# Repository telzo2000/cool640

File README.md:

# cool640

<br>

## What is cool640？

cool640 is 4X5 macro pad keyboard.
<br>
If you align the two, you will have a split keyboard.
<br><br>
cool640は4X5のマクロパッドキーボードです。
<br>
cool640は二つ揃えると、分割キーボードになります。
<br><br>
You can choose either pro micro or raspberry pi pico to use.
<br><br>
pro microかraspberry pi picoのどちらか一つを選んで使うことができます。

<br><br>
You can choose either choc switch or cherry mx switch to use.
<br>
Chocスイッチか CHERRY MXスイッチのどちらか一つを選んで使うことができます。

<br>
The size of the PCB is within 100mmX100mm.
<br>
It will be distributed on booth in the future, but you can freely use the data here and place an order with the PCB manufacturer.
<br><br>
PCBのサイズは、100mmX100mm以内です。
<br>
将来、boothにて頒布しますが、ここにあるデータを自由に使い、各自がPCB製造元に発注しても構いません。
<br><br>
I do not take any responsibility for the data that you freely use.
<br>
Please use at your own risk.
<br><br>
各自が自由に使ったデータについては、私は一切の責任を負いません。
<br>
自己責任で利用してください。
<br>

## Build Guide
https://github.com/telzo2000/cool640/blob/main/buildguide_for_cool640.md

<br>

## Firmware
https://github.com/telzo2000/cool640/tree/main/firmware

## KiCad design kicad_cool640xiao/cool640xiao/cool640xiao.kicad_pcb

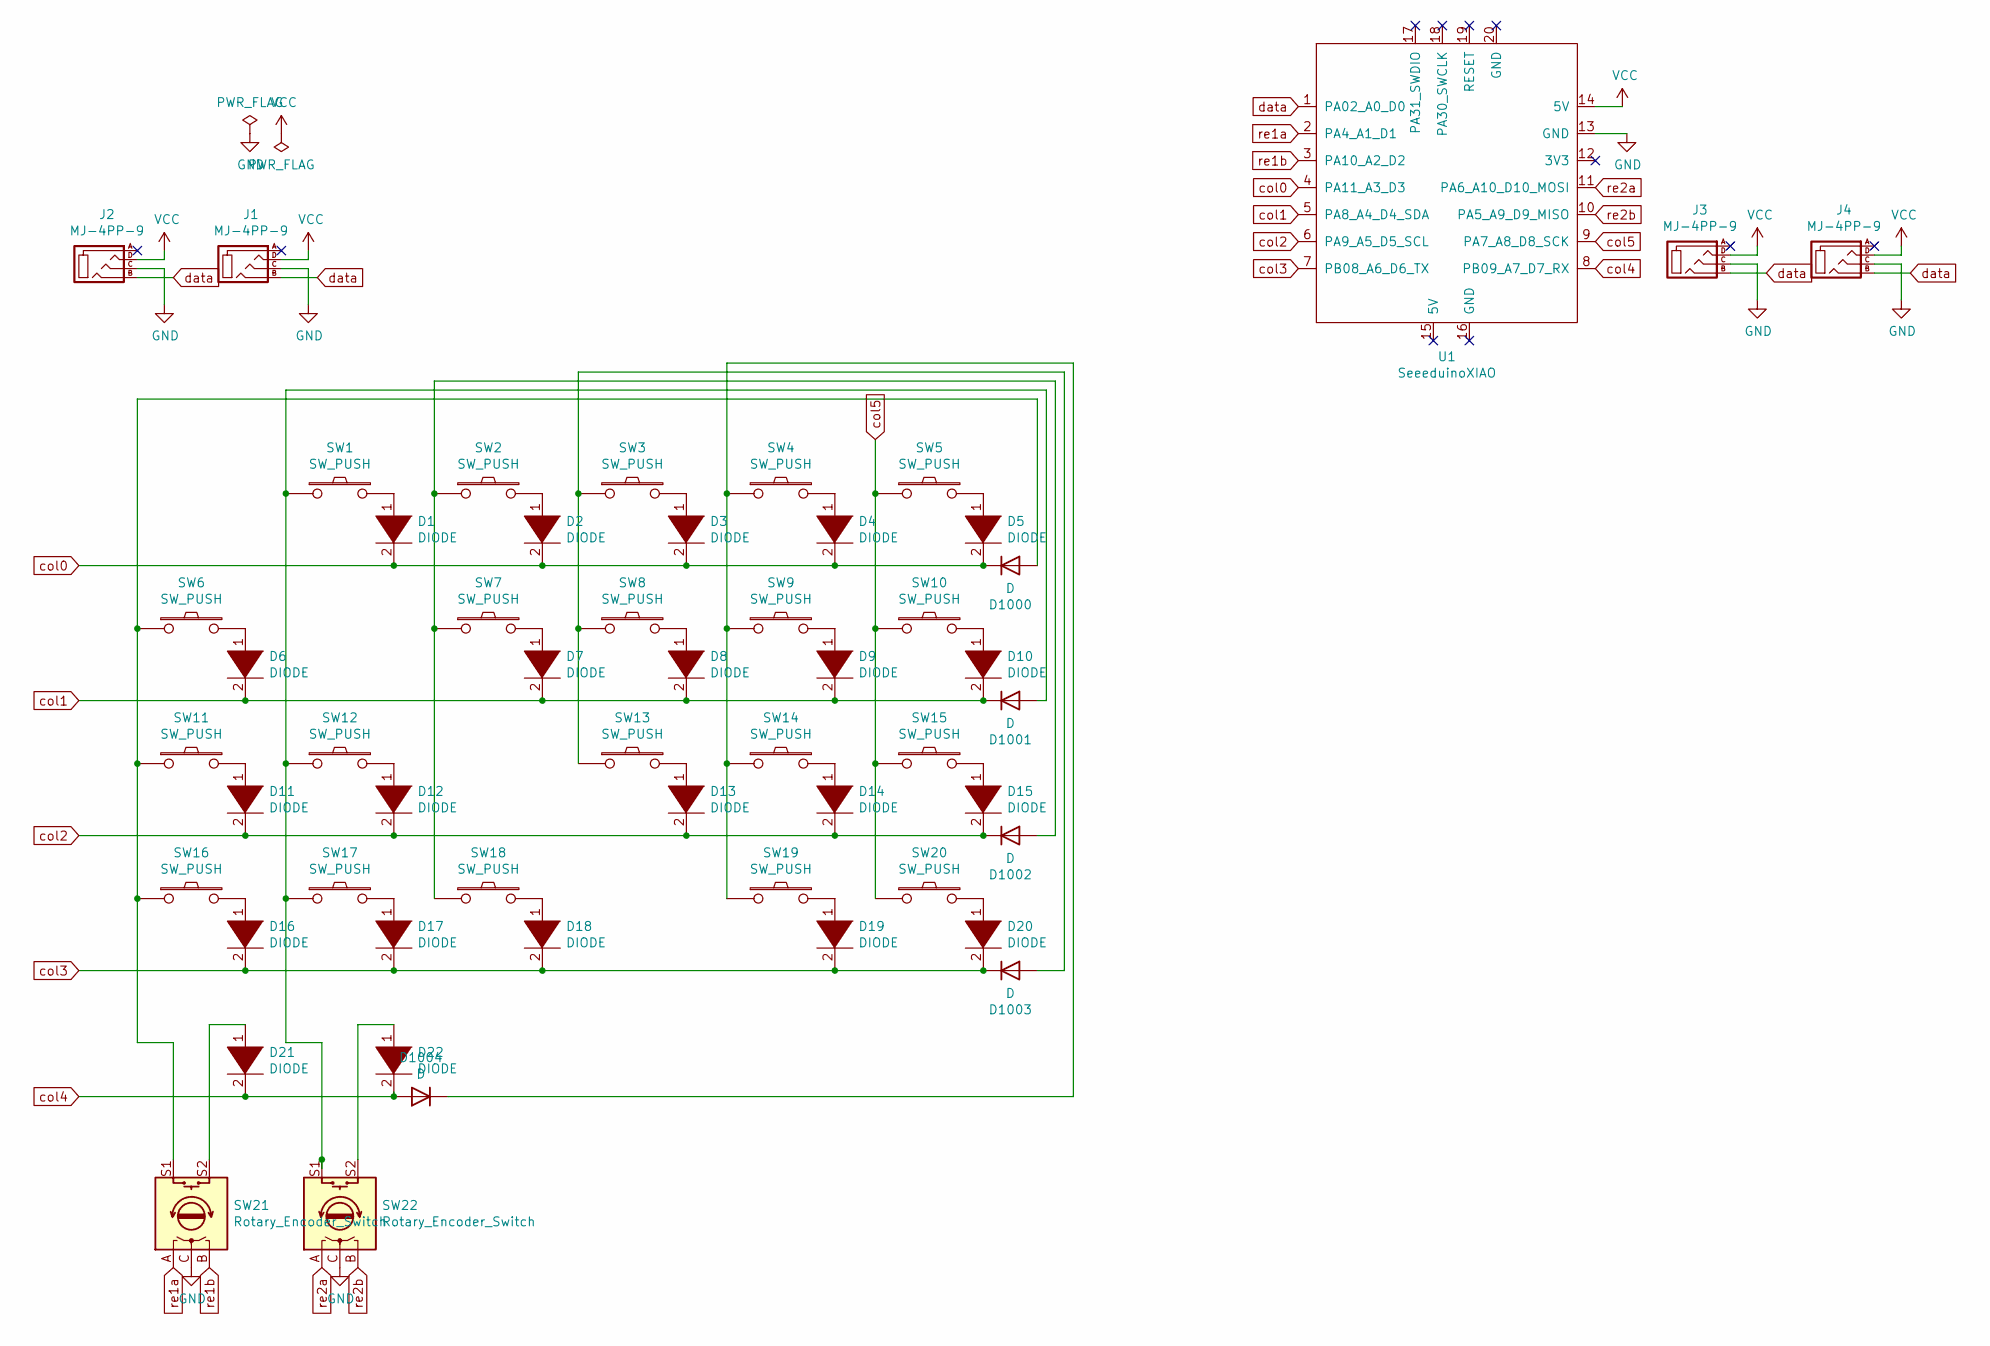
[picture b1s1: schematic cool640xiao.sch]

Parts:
D1, D2, D3, D4, D5, D6, D7, D8, D9, D10, D11, D12, D13, D14, D15, D16, D17, D18, D19, D20, D21, D22: DIODE; D3_TH_SMD
D1000, D1001, D1002, D1003, D1004: D; D3_TH_SMD
J1, J2: MJ-4PP-9; MJ-4PP-9_1side
J3, J4: MJ-4PP-9; TRSpad
SW1, SW2, SW3, SW4, SW5, SW6, SW7, SW8, SW9, SW10, SW11, SW12, SW13, SW14, SW15, SW16, SW17, SW18, SW19, SW20: SW_PUSH; CherryMX_MidHeight_Choc_Hotswap_katagawa
SW21, SW22: Rotary_Encoder_Switch; RotaryEncoder_Alps_EC12E-Switch_Vertical_H20mm_CircularMoun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
U1: SeeeduinoXIAO; XIAO_RP2040

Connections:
GND: J1.C, J2.C, J3.C, J4.C, SW21.C, SW22.C, U1.13 (GND)
unnamed: D1.1 (K), SW1.2
unnamed: D2.1 (K), SW2.2
unnamed: D3.1 (K), SW3.2
unnamed: D4.1 (K), SW4.2
unnamed: D5.1 (K), SW5.2
unnamed: D6.1 (K), SW6.2
unnamed: D7.1 (K), SW7.2
unnamed: D8.1 (K), SW8.2
unnamed: D9.1 (K), SW9.2
unnamed: D10.1 (K), SW10.2
unnamed: D11.1 (K), SW11.2
unnamed: D12.1 (K), SW12.2
unnamed: D13.1 (K), SW13.2
unnamed: D14.1 (K), SW14.2
unnamed: D15.1 (K), SW15.2
unnamed: D16.1 (K), SW16.2
unnamed: D17.1 (K), SW17.2
unnamed: D18.1 (K), SW18.2
unnamed: D19.1 (K), SW19.2
unnamed: D20.1 (K), SW20.2
unnamed: D21.1 (K), SW21.S2
unnamed: D22.1 (K), SW22.S2
unnamed: D1000.2 (A), SW6.1, SW11.1, SW16.1, SW21.S1
unnamed: D1001.2 (A), SW1.1, SW12.1, SW17.1, SW22.S1
unnamed: D1002.2 (A), SW2.1, SW7.1, SW18.1
unnamed: D1003.2 (A), SW3.1, SW8.1, SW13.1
unnamed: D1004.1 (K), SW4.1, SW9.1, SW14.1, SW19.1
VCC: J1.D, J2.D, J3.D, J4.D, U1.14 (5V)
col0: D1.2 (A), D2.2 (A), D3.2 (A), D4.2 (A), D5.2 (A), D1000.1 (K), U1.4 (PA11_A3_D3)
col1: D6.2 (A), D7.2 (A), D8.2 (A), D9.2 (A), D10.2 (A), D1001.1 (K), U1.5 (PA8_A4_D4_SDA)
col2: D11.2 (A), D12.2 (A), D13.2 (A), D14.2 (A), D15.2 (A), D1002.1 (K), U1.6 (PA9_A5_D5_SCL)
col3: D16.2 (A), D17.2 (A), D18.2 (A), D19.2 (A), D20.2 (A), D1003.1 (K), U1.7 (PB08_A6_D6_TX)
col4: D21.2 (A), D22.2 (A), D1004.2 (A), U1.8 (PB09_A7_D7_RX)
col5: SW5.1, SW10.1, SW15.1, SW20.1, U1.9 (PA7_A8_D8_SCK)
data: J1.B, J2.B, J3.B, J4.B, U1.1 (PA02_A0_D0)
re1a: SW21.A, U1.2 (PA4_A1_D1)
re1b: SW21.B, U1.3 (PA10_A2_D2)
re2a: SW22.A, U1.11 (PA6_A10_D10_MOSI)
re2b: SW22.B, U1.10 (PA5_A9_D9_MISO)

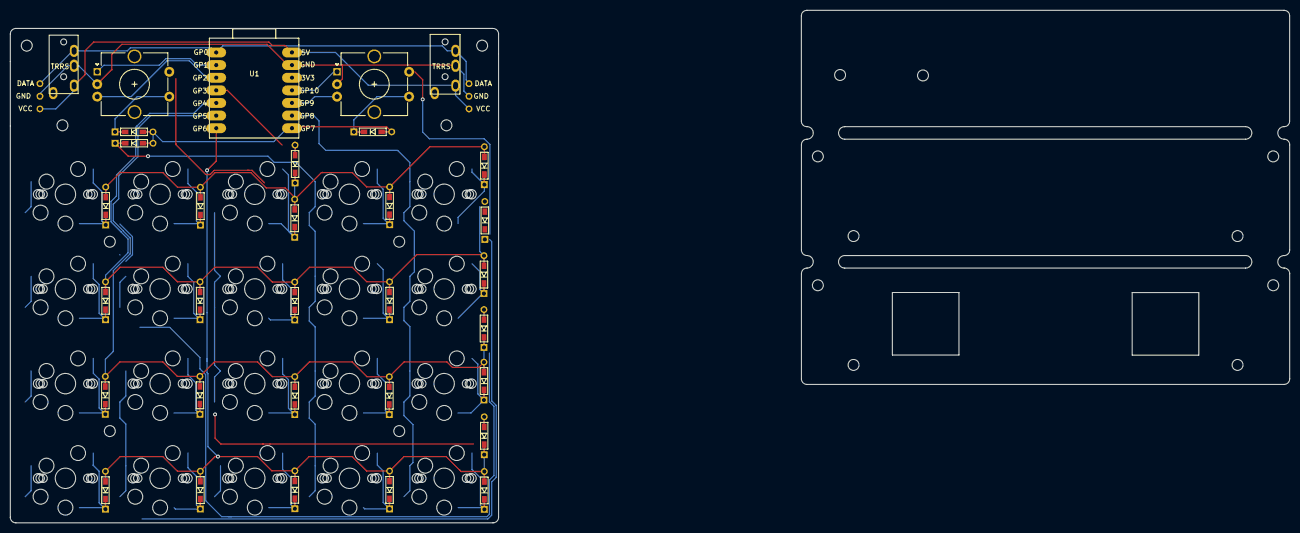
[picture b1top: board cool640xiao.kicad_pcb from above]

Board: 2 copper layers, 257.4 x 103.1 mm, 54 parts (0 on the bottom side), 40 nets.

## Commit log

2022-02-25 Create readme_for_gbr
2022-02-25 Create buildguide_for_cool640
